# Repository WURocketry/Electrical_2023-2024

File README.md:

# Electrical
Electrical / Software Development

* Circuit CAD
* Software

### Subteam Folders
Subteams are free to modify their own folder as they like - keep all your subteam related files/articles/figures within that folder.

### Subteam Branches
The "main" Electrical repository is organized into 2 subteam development branches:

* "dev/avionics"
* "dev/payload"
* "dev/airbrakes"

Subteam changes should be pushed and pull requests made only to the respective development subteam branch!

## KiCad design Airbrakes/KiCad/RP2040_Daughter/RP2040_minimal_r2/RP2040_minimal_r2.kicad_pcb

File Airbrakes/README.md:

# Airbrakes Electrical

Folder for development of airbrake electrical mechanisms including:
> * Trajectory simulator
> * VLT
> * Actuation control algorithms
> * Eagle CADs

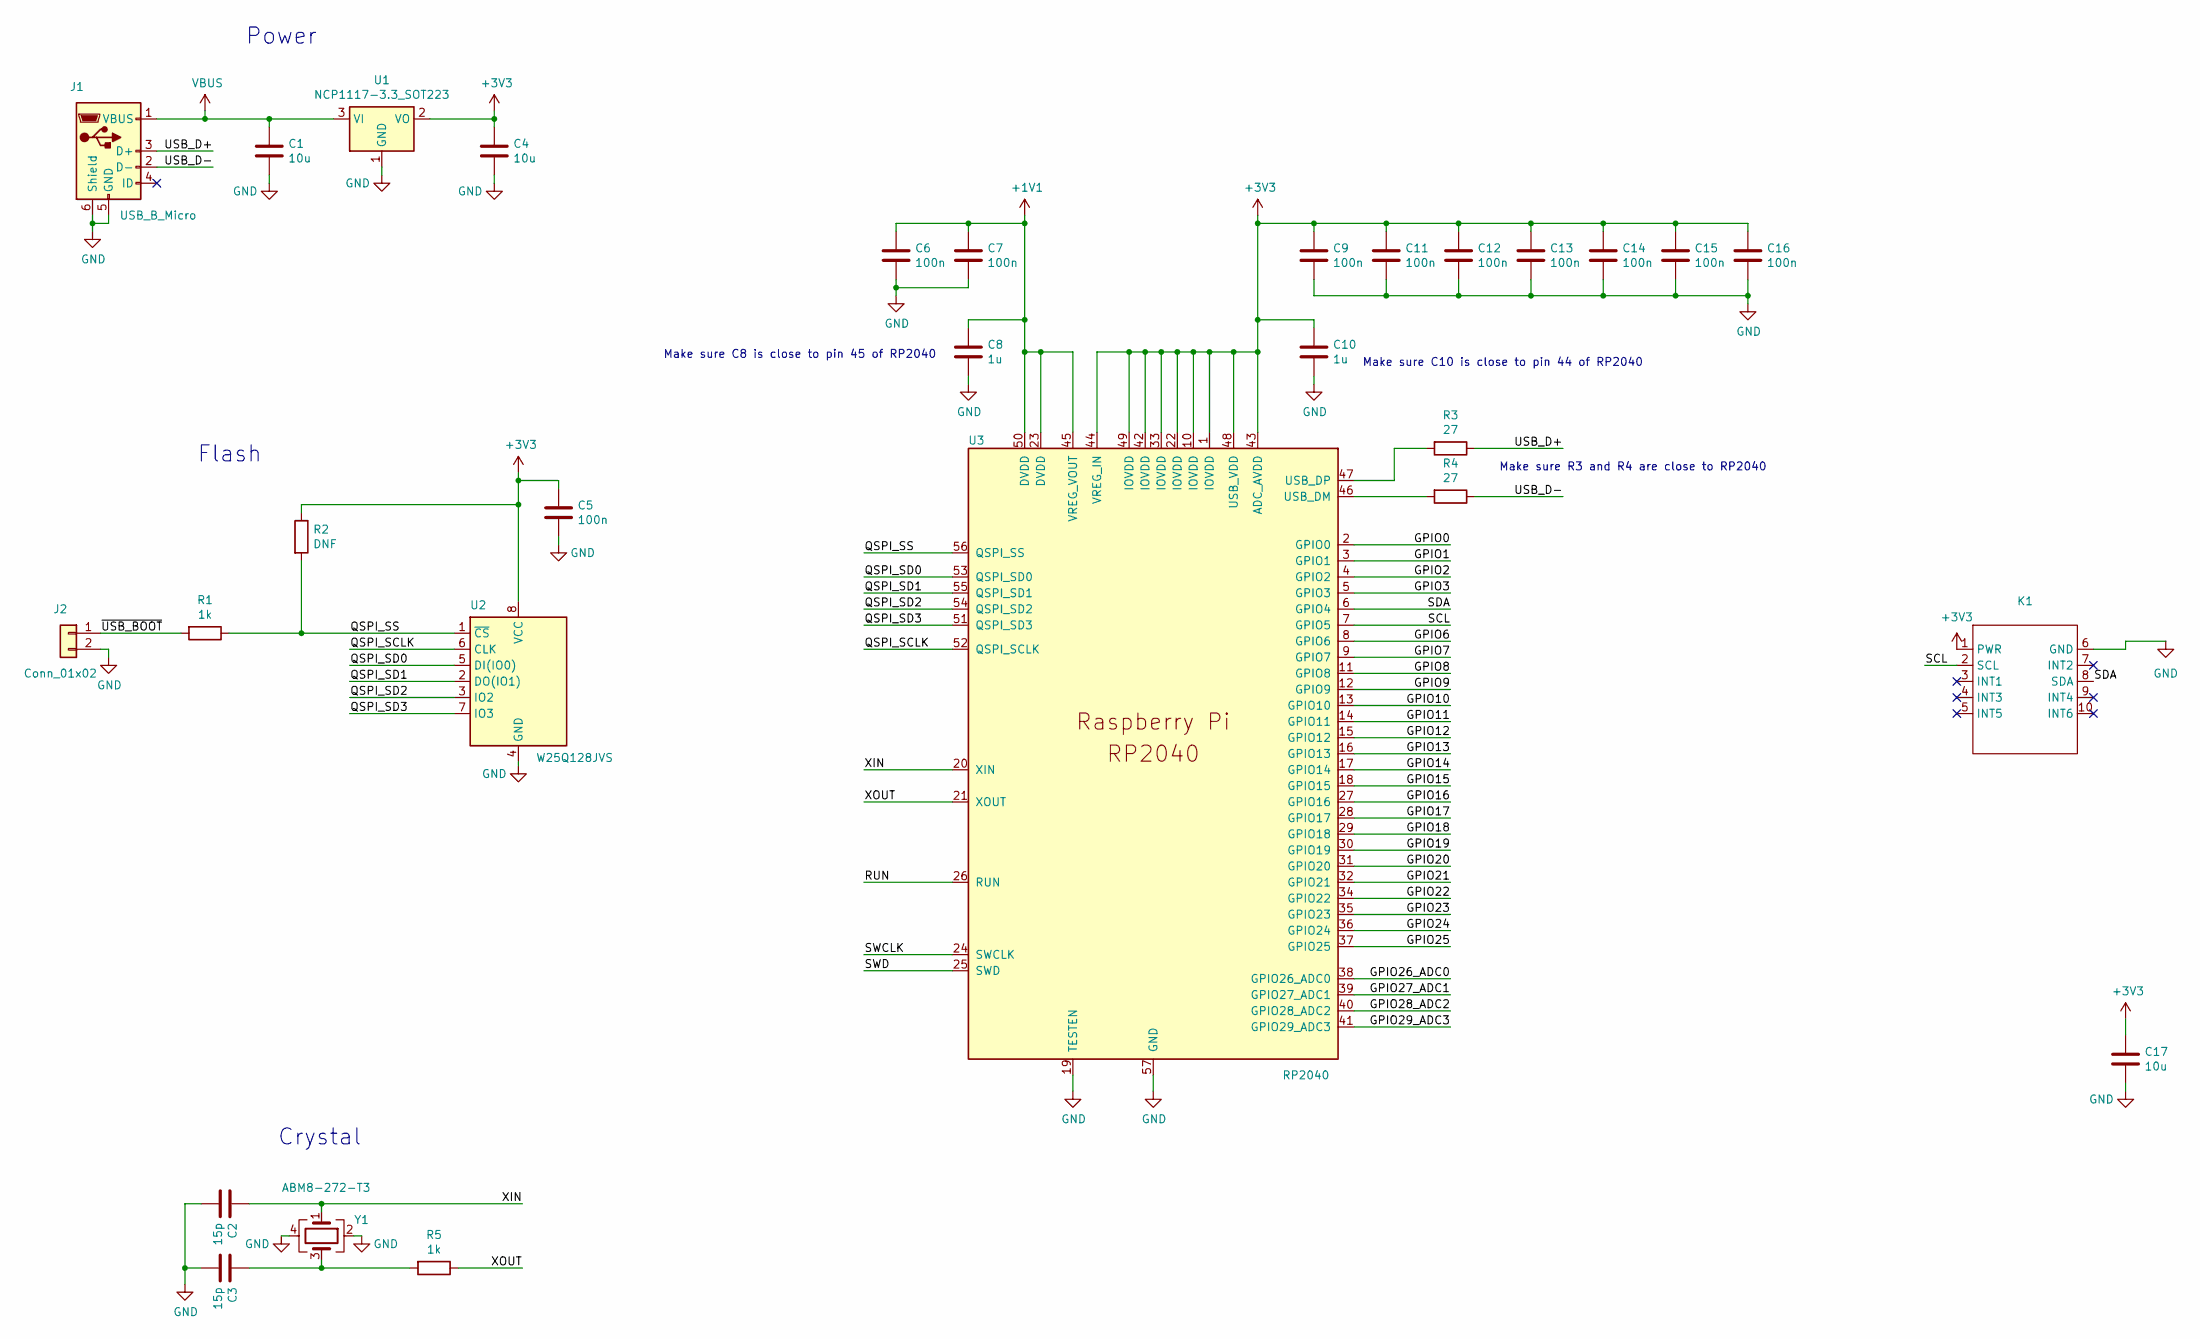
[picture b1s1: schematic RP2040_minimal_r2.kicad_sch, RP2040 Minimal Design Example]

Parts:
C1, C4, C17: 10u; C_0805_2012Metric
C2, C3: 15p; C_0402_1005Metric
C5, C6, C7, C9, C11, C12, C13, C14, C15, C16: 100n; C_0402_1005Metric
C8, C10: 1u; C_0402_1005Metric
J1: USB_B_Micro; USB_Micro-B_Amphenol_10103594-0001LF_Horizontal_modified
J2: Conn_01x02; PinHeader_1x02_P2.54mm_Vertical
K1: 12_Pin_Edge_Connector
R1, R5: 1k; R_0402_1005Metric
R2: DNF; R_0402_1005Metric
R3, R4: 27; R_0402_1005Metric
U1: NCP1117-3.3_SOT223; SOT-223-3_TabPin2
U2: W25Q128JVS; SOIC-8_5.23x5.23mm_P1.27mm
U3: RP2040; RP2040-QFN-56
Y1: ABM8-272-T3; Crystal_SMD_3225-4Pin_3.2x2.5mm

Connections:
+1V1: C6.1, C7.1, C8.1, U3.23 (DVDD), U3.45 (VREG_VOUT), U3.50 (DVDD)
+3V3: C4.1, C5.1, C9.1, C10.1, C11.1, C12.1, C13.1, C14.1, C15.1, C16.1, C17.1, K1.1 (PWR), R2.1, U1.2 (VO), U2.8 (VCC), U3.1 (IOVDD), U3.10 (IOVDD), U3.22 (IOVDD), U3.33 (IOVDD), U3.42 (IOVDD), U3.43 (ADC_AVDD), U3.44 (VREG_IN), U3.48 (USB_VDD), U3.49 (IOVDD)
/GPIO0: U3.2 (GPIO0)
/GPIO1: U3.3 (GPIO1)
/GPIO2: U3.4 (GPIO2)
/GPIO3: U3.5 (GPIO3)
/GPIO6: U3.8 (GPIO6)
/GPIO7: U3.9 (GPIO7)
/GPIO8: U3.11 (GPIO8)
/GPIO9: U3.12 (GPIO9)
/GPIO10: U3.13 (GPIO10)
/GPIO11: U3.14 (GPIO11)
/GPIO12: U3.15 (GPIO12)
/GPIO13: U3.16 (GPIO13)
/GPIO14: U3.17 (GPIO14)
/GPIO15: U3.18 (GPIO15)
/GPIO16: U3.27 (GPIO16)
/GPIO17: U3.28 (GPIO17)
/GPIO18: U3.29 (GPIO18)
/GPIO19: U3.30 (GPIO19)
/GPIO20: U3.31 (GPIO20)
/GPIO21: U3.32 (GPIO21)
/GPIO22: U3.34 (GPIO22)
/GPIO23: U3.35 (GPIO23)
/GPIO24: U3.36 (GPIO24)
/GPIO25: U3.37 (GPIO25)
/GPIO26_ADC0: U3.38 (GPIO26_ADC0)
/GPIO27_ADC1: U3.39 (GPIO27_ADC1)
/GPIO28_ADC2: U3.40 (GPIO28_ADC2)
/GPIO29_ADC3: U3.41 (GPIO29_ADC3)
/QSPI_SCLK: U2.6 (CLK), U3.52 (QSPI_SCLK)
/QSPI_SD0: U2.5 (DI(IO0)), U3.53 (QSPI_SD0)
/QSPI_SD1: U2.2 (DO(IO1)), U3.55 (QSPI_SD1)
/QSPI_SD2: U2.3 (IO2), U3.54 (QSPI_SD2)
/QSPI_SD3: U2.7 (IO3), U3.51 (QSPI_SD3)
/QSPI_SS: R1.1, R2.2, U2.1 (~CS), U3.56 (QSPI_SS)
/RUN: U3.26 (RUN)
/SCL: K1.2 (SCL), U3.7 (GPIO5)
/SDA: K1.8 (SDA), U3.6 (GPIO4)
/SWCLK: U3.24 (SWCLK)
/SWD: U3.25 (SWD)
/USB_D+: J1.3 (D+), R3.1
/USB_D-: J1.2 (D-), R4.1
/XIN: C2.1, U3.20 (XIN), Y1.1
/XOUT: R5.1, U3.21 (XOUT)
/~USB_BOOT: J2.1, R1.2
GND: C1.2, C2.2, C3.2, C4.2, C5.2, C6.2, C7.2, C8.2, C9.2, C10.2, C11.2, C12.2, C13.2, C14.2, C15.2, C16.2, C17.2, J1.5 (GND), J1.6 (Shield), J2.2, K1.6 (GND), U1.1 (GND), U2.4 (GND), U3.19 (TESTEN), U3.57 (GND), Y1.2, Y1.4
unnamed: C3.1, R5.2, Y1.3
unnamed: R4.2, U3.46 (USB_DM)
unnamed: R3.2, U3.47 (USB_DP)
VBUS: C1.1, J1.1 (VBUS), U1.3 (VI)

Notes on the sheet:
Power
Crystal
Make sure C8 is close to pin 45 of RP2040
Make sure C10 is close to pin 44 of RP2040
Make sure R3 and R4 are close to RP2040
Flash

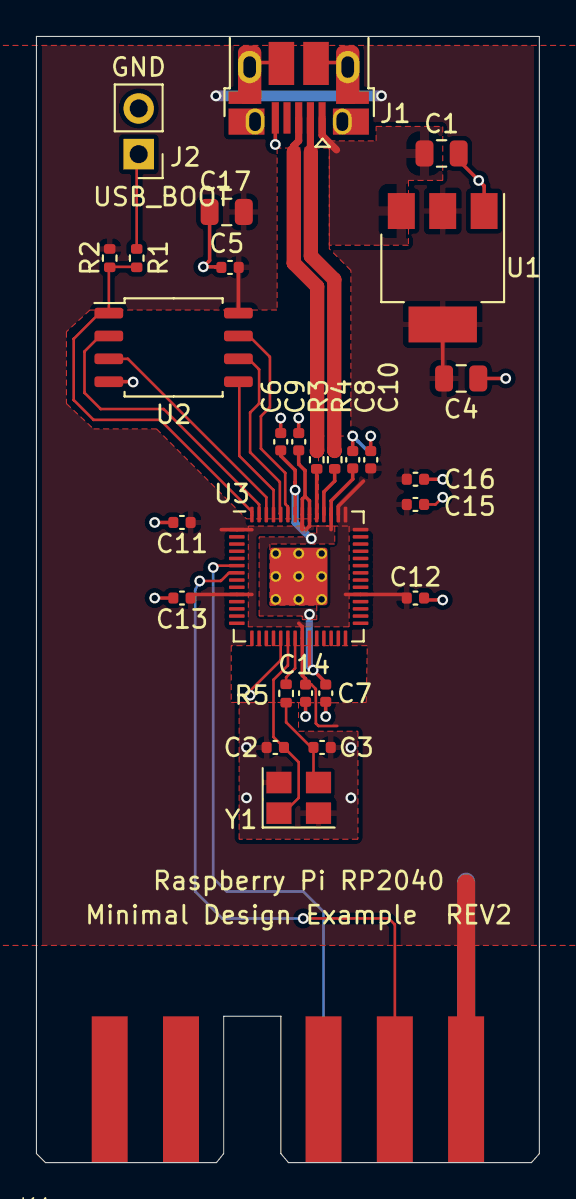
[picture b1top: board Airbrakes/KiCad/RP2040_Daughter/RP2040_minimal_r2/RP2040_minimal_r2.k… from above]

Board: 2 copper layers, 27.9 x 62.6 mm, 29 parts (0 on the bottom side), 20 nets.

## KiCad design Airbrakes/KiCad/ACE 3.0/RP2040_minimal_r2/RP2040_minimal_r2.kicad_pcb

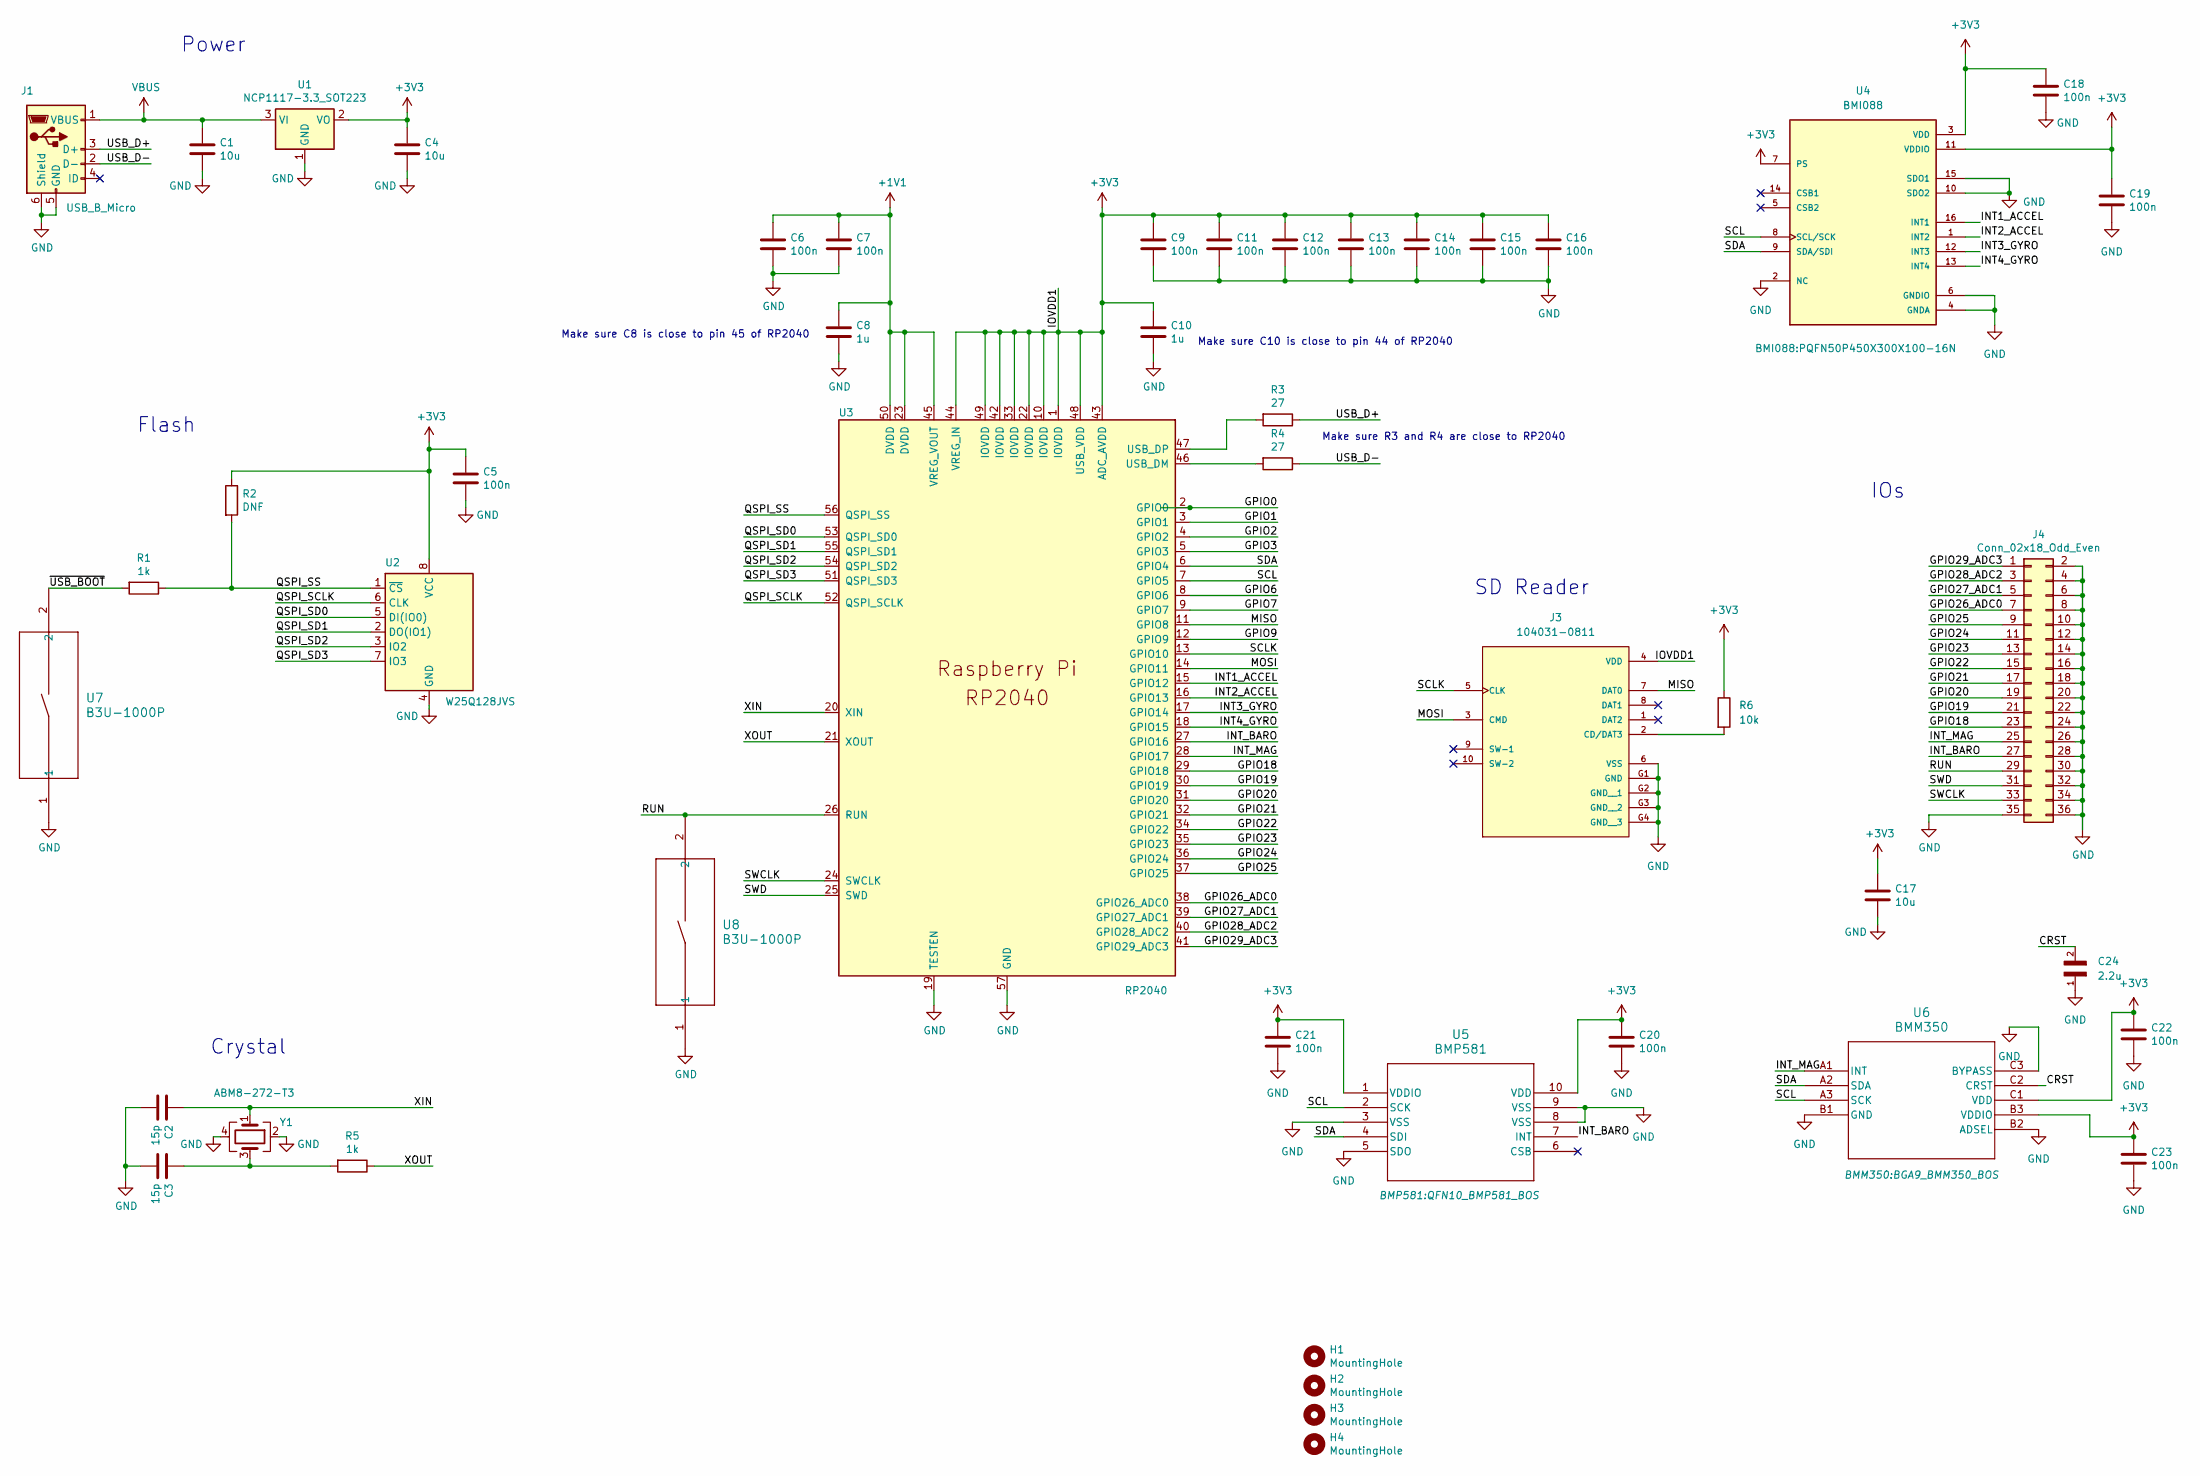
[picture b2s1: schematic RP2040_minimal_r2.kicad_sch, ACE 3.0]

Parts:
C1, C4, C17: 10u; C_0805_2012Metric
C2, C3: 15p; C_0402_1005Metric
C5, C6, C7, C9, C11, C12, C13, C14, C15, C16, C18, C19, C20, C21, C22, C23: 100n; C_0402_1005Metric
C8, C10: 1u; C_0402_1005Metric
C24: 2.2u; CAPC2012X55N
H1, H2, H3, H4: MountingHole; MountingHole_2.7mm_M2.5
J1: USB_B_Micro; USB_Micro-B_Amphenol_10103594-0001LF_Horizontal_modified
J3: 104031-0811; MOLEX_104031-0811; PARTREV B2
J4: Conn_02x18_Odd_Even; PinHeader_2x18_P2.54mm_Vertical
R1, R5: 1k; R_0402_1005Metric
R2: DNF; R_0402_1005Metric
R3, R4: 27; R_0402_1005Metric
R6: 10k; R_0402_1005Metric
U1: NCP1117-3.3_SOT223; SOT-223-3_TabPin2
U2: W25Q128JVS; SOIC-8_5.23x5.23mm_P1.27mm
U3: RP2040; RP2040-QFN-56
U4: BMI088; PQFN50P450X300X100-16N
U5: BMP581; QFN10_BMP581_BOS
U6: BMM350; BGA9_BMM350_BOS
U7, U8: B3U-1000P; SW_SPST_B3U-1000P
Y1: ABM8-272-T3; Crystal_SMD_3225-4Pin_3.2x2.5mm

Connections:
+1V1: C6.1, C7.1, C8.1, U3.23 (DVDD), U3.45 (VREG_VOUT), U3.50 (DVDD)
+3V3: C4.1, C5.1, C9.1, C10.1, C11.1, C12.1, C13.1, C14.1, C15.1, C16.1, C17.1, C18.1, C19.1, C20.1, C21.1, C22.1, C23.1, J3.4 (VDD), R2.1, R6.1, U1.2 (VO), U2.8 (VCC), U3.1 (IOVDD), U3.10 (IOVDD), U3.22 (IOVDD), U3.33 (IOVDD), U3.42 (IOVDD), U3.43 (ADC_AVDD), U3.44 (VREG_IN), U3.48 (USB_VDD), U3.49 (IOVDD), U4.3 (VDD), U4.7 (PS), U4.11 (VDDIO), U5.1 (VDDIO), U5.10 (VDD), U6.B3 (VDDIO), U6.C1 (VDD)
/CRST: C24.2, U6.C2 (CRST)
/GPIO0: U3.2 (GPIO0)
/GPIO1: U3.3 (GPIO1)
/GPIO2: U3.4 (GPIO2)
/GPIO3: U3.5 (GPIO3)
/GPIO6: U3.8 (GPIO6)
/GPIO7: U3.9 (GPIO7)
/GPIO9: U3.12 (GPIO9)
/GPIO18: J4.23, U3.29 (GPIO18)
/GPIO19: J4.21, U3.30 (GPIO19)
/GPIO20: J4.19, U3.31 (GPIO20)
/GPIO21: J4.17, U3.32 (GPIO21)
/GPIO22: J4.15, U3.34 (GPIO22)
/GPIO23: J4.13, U3.35 (GPIO23)
/GPIO24: J4.11, U3.36 (GPIO24)
/GPIO25: J4.9, U3.37 (GPIO25)
/GPIO26_ADC0: J4.7, U3.38 (GPIO26_ADC0)
/GPIO27_ADC1: J4.5, U3.39 (GPIO27_ADC1)
/GPIO28_ADC2: J4.3, U3.40 (GPIO28_ADC2)
/GPIO29_ADC3: J4.1, U3.41 (GPIO29_ADC3)
/INT1_ACCEL: U3.15 (GPIO12), U4.16 (INT1)
/INT2_ACCEL: U3.16 (GPIO13), U4.1 (INT2)
/INT3_GYRO: U3.17 (GPIO14), U4.12 (INT3)
/INT4_GYRO: U3.18 (GPIO15), U4.13 (INT4)
/INT_BARO: J4.27, U3.27 (GPIO16), U5.7 (INT)
/INT_MAG: J4.25, U3.28 (GPIO17), U6.A1 (INT)
/MISO: J3.7 (DAT0), U3.11 (GPIO8)
/MOSI: J3.3 (CMD), U3.14 (GPIO11)
/QSPI_SCLK: U2.6 (CLK), U3.52 (QSPI_SCLK)
/QSPI_SD0: U2.5 (DI(IO0)), U3.53 (QSPI_SD0)
/QSPI_SD1: U2.2 (DO(IO1)), U3.55 (QSPI_SD1)
/QSPI_SD2: U2.3 (IO2), U3.54 (QSPI_SD2)
/QSPI_SD3: U2.7 (IO3), U3.51 (QSPI_SD3)
/QSPI_SS: R1.1, R2.2, U2.1 (~CS), U3.56 (QSPI_SS)
/RUN: J4.29, U3.26 (RUN), U8.2
/SCL: U3.7 (GPIO5), U4.8 (SCL/SCK), U5.2 (SCK), U6.A3 (SCK)
/SCLK: J3.5 (CLK), U3.13 (GPIO10)
/SDA: U3.6 (GPIO4), U4.9 (SDA/SDI), U5.4 (SDI), U6.A2 (SDA)
/SWCLK: J4.33, U3.24 (SWCLK)
/SWD: J4.31, U3.25 (SWD)
/USB_D+: J1.3 (D+), R3.1
/USB_D-: J1.2 (D-), R4.1
/XIN: C2.1, U3.20 (XIN), Y1.1
/XOUT: R5.1, U3.21 (XOUT)
/~USB_BOOT: R1.2, U7.2
GND: C1.2, C2.2, C3.2, C4.2, C5.2, C6.2, C7.2, C8.2, C9.2, C10.2, C11.2, C12.2, C13.2, C14.2, C15.2, C16.2, C17.2, C18.2, C19.2, C20.2, C21.2, C22.2, C23.2, C24.1, J1.5 (GND), J1.6 (Shield), J3.6 (VSS), J3.G1 (GND), J3.G2 (GND__1), J3.G3 (GND__2), J3.G4 (GND__3), J4.2, J4.4, J4.6, J4.8, J4.10, J4.12, J4.14, J4.16, J4.18, J4.20, J4.22, J4.24, J4.26, J4.28, J4.30, J4.32, J4.34, J4.35, J4.36, U1.1 (GND), U2.4 (GND), U3.19 (TESTEN), U3.57 (GND), U4.2 (NC), U4.4 (GNDA), U4.6 (GNDIO), U4.10 (SDO2), U4.15 (SDO1), U5.3 (VSS), U5.5 (SDO), U5.8 (VSS), U5.9 (VSS), U6.B1 (GND), U6.B2 (ADSEL), U6.C3 (BYPASS), U7.1, U8.1, Y1.2, Y1.4
unnamed: C3.1, R5.2, Y1.3
unnamed: J3.2 (CD/DAT3), R6.2
unnamed: R4.2, U3.46 (USB_DM)
unnamed: R3.2, U3.47 (USB_DP)
VBUS: C1.1, J1.1 (VBUS), U1.3 (VI)

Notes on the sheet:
IOs
Power
Crystal
Make sure C8 is close to pin 45 of RP2040
SD Reader
Make sure C10 is close to pin 44 of RP2040
Make sure R3 and R4 are close to RP2040
Flash

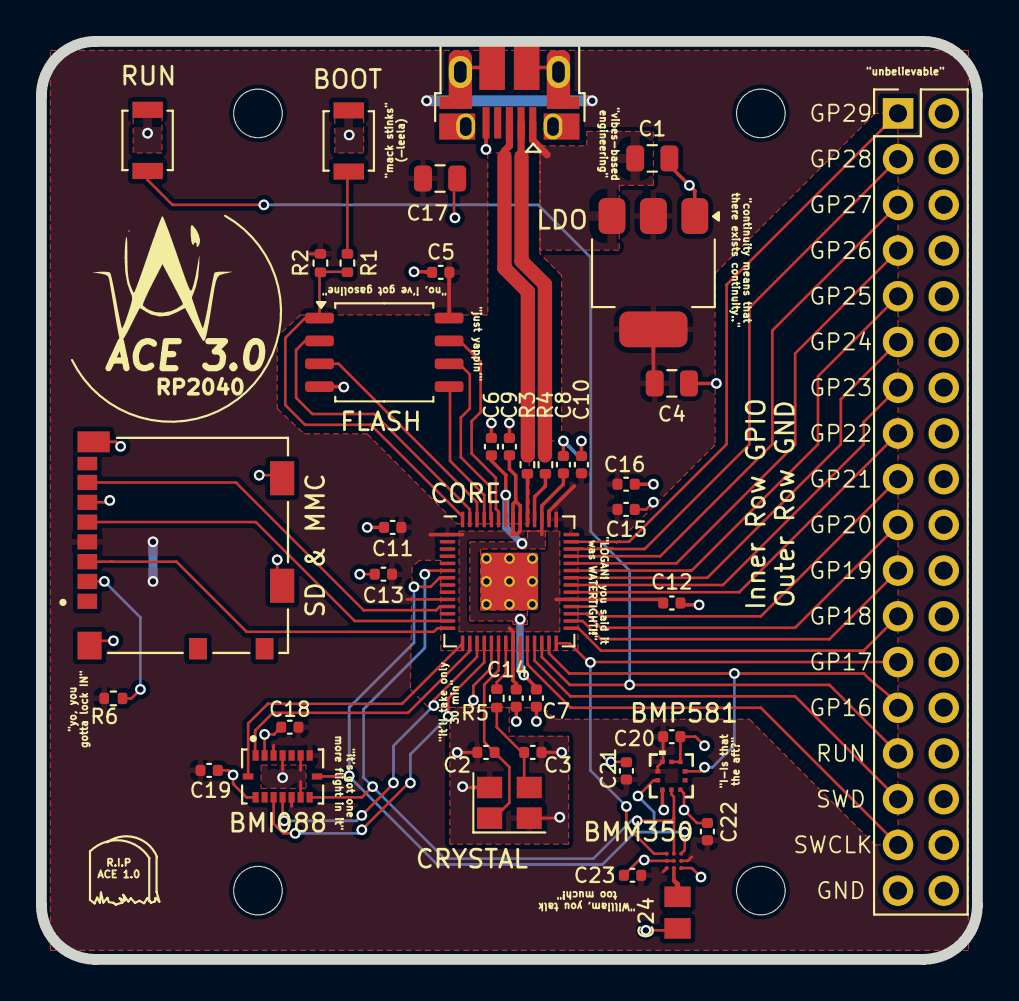
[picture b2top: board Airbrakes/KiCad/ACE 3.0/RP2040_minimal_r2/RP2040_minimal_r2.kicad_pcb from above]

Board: 2 copper layers, 52.0 x 51.0 mm, 46 parts (0 on the bottom side), 46 nets.

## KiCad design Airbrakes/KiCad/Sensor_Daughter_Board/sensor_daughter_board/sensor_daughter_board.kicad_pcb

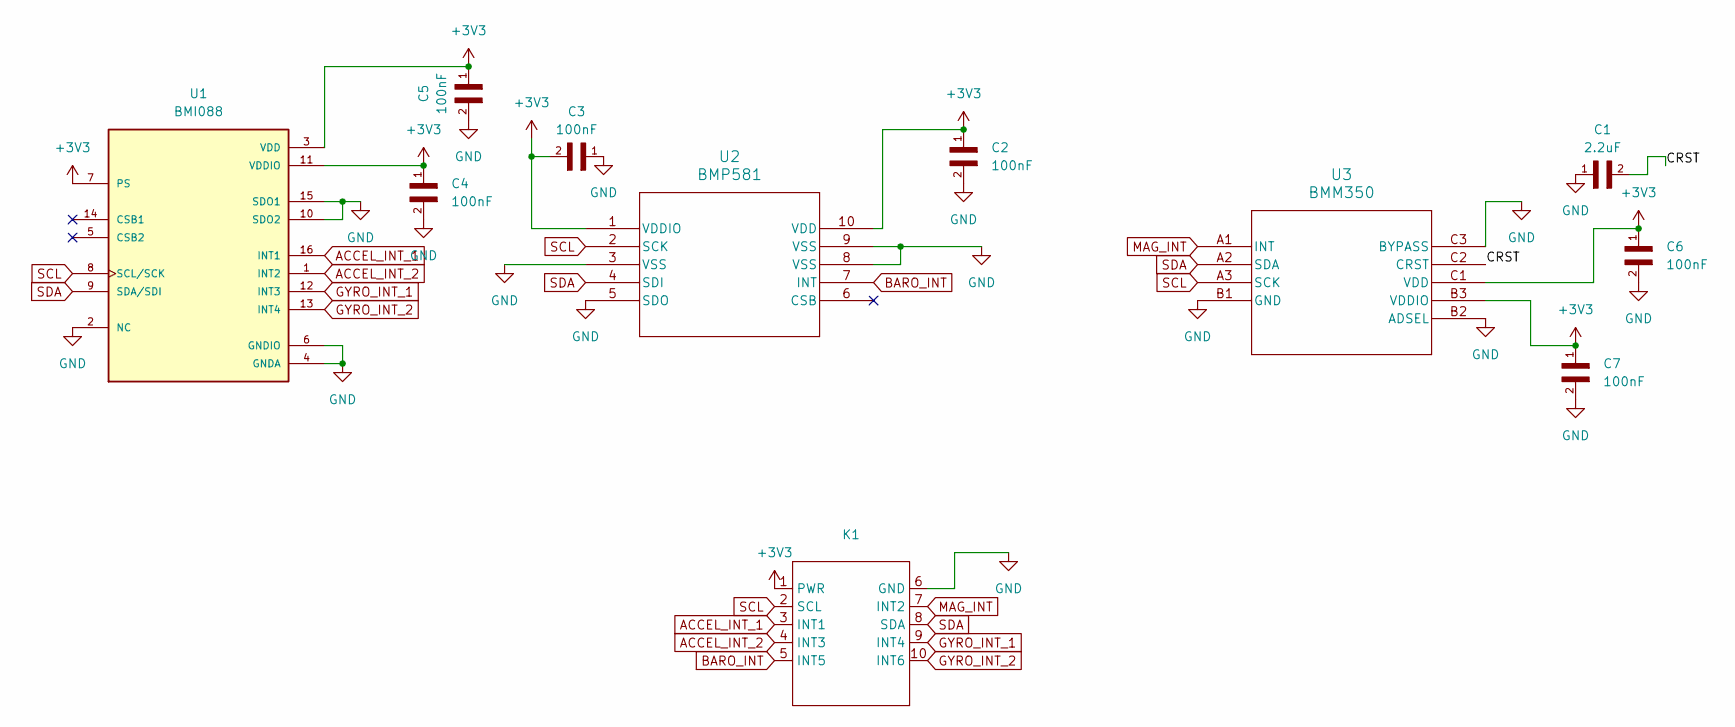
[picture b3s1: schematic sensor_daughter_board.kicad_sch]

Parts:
C1: 2.2uF; CAPC2012X55N
C2, C3, C4, C5, C6, C7: 100nF; CAPC1005X55N
K1: 12_Pin_Edge_Connector
U1: BMI088; PQFN50P450X300X100-16N
U2: BMP581; QFN10_BMP581_BOS
U3: BMM350; BGA9_BMM350_BOS

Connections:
+3V3: C2.1, C3.2, C4.1, C5.1, C6.1, C7.1, K1.1 (PWR), U1.3 (VDD), U1.7 (PS), U1.11 (VDDIO), U2.1 (VDDIO), U2.10 (VDD), U3.B3 (VDDIO), U3.C1 (VDD)
/CRST: C1.2, U3.C2 (CRST)
ACCEL_INT_1: K1.3 (INT1), U1.16 (INT1)
ACCEL_INT_2: K1.4 (INT3), U1.1 (INT2)
BARO_INT: K1.5 (INT5), U2.7 (INT)
GND: C1.1, C2.2, C3.1, C4.2, C5.2, C6.2, C7.2, K1.6 (GND), U1.2 (NC), U1.4 (GNDA), U1.6 (GNDIO), U1.10 (SDO2), U1.15 (SDO1), U2.3 (VSS), U2.5 (SDO), U2.8 (VSS), U2.9 (VSS), U3.B1 (GND), U3.B2 (ADSEL), U3.C3 (BYPASS)
GYRO_INT_1: K1.9 (INT4), U1.12 (INT3)
GYRO_INT_2: K1.10 (INT6), U1.13 (INT4)
MAG_INT: K1.7 (INT2), U3.A1 (INT)
SCL: K1.2 (SCL), U1.8 (SCL/SCK), U2.2 (SCK), U3.A3 (SCK)
SDA: K1.8 (SDA), U1.9 (SDA/SDI), U2.4 (SDI), U3.A2 (SDA)

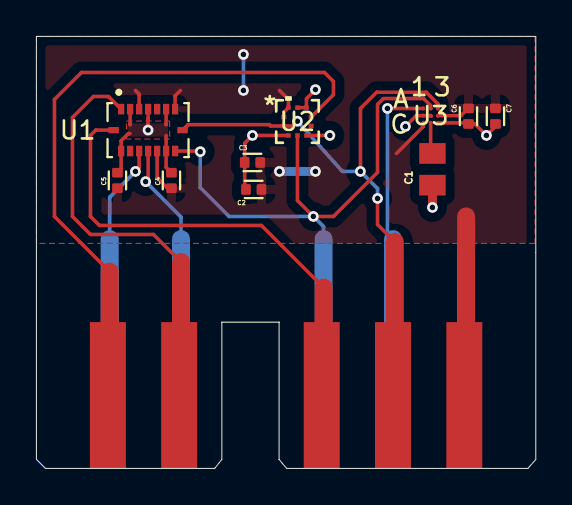
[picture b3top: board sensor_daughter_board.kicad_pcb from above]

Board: 2 copper layers, 27.7 x 24.0 mm, 11 parts (0 on the bottom side), 11 nets.

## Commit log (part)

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2023-10-22 Fixed delta timing from comments
2023-10-22 base station script
2023-10-22 Update main.cpp
    Updated standby state
2023-10-22 Initial FSM integration for ACE (#47)
    * Update main.cpp
    Implemented FSM transitions
    * Update main.cpp
    Updated standby state
    ---------
2023-10-23 Create vlt.h
    Creates velocity look-up table for Full Scale as header file
2023-10-24 move vlt table
2023-10-24 fixing merge conflicts
2023-10-25 Modified delta timing and changed time status to unsigned long
2023-10-25 Add BAD approximations for mass change over time and drag dependence on Vel
2023-10-25 Make delta timing discrete and replace COMPUTE poll condition
    * Last time variables are incremented by respective delta times
    * COMPUTE runs at multiples of 4 SAMPLE polls
2023-10-25 Delta timing for components (#46)
    * Fixed delta timing from comments
    * Fixed delta timing, no compiler errors
    * Modified delta timing and changed time status to unsigned long
    ---------
2023-10-29 adding neopixel stuff, compiles
2023-10-29 Revert "Payload/small csv"
2023-11-01 FlightMonitor header file
2023-11-01 LinearInterp attempt
2023-11-01 PID Control/Servo Test Control File
2023-11-01 Update main.ino (#54)
    * Update main.ino
    * Update main.ino
2023-11-02 Add simulation OR data sample
2023-11-02 Add necessary files and definitions
2023-11-03 Add necessary files and definitions (#57)
2023-11-03 Add simulation OR data sample (#56)
    * Add simulation OR data sample
    * Handle negative simulation time exception case
    ---------
2023-11-03 Implement all state transtions
2023-11-03 Create Persistences
    landing transition does not behave as expected.
2023-11-04 Fix Bounds
2023-11-04 hello world on receiving end and server end both work
2023-11-04 Change persistence and remove include
2023-11-04 Added not about removing wait for serial connection for flight
2023-11-04 Attempt at preprocessor stuff
    Also added something to .ini to make the sdram.h work... it did not
2023-11-05 Implement all state transitions (#58)
    * Implement all state transtions
    * Create Persistences
    landing transition does not behave as expected.
    * Move Evaluation of Flight Monitor
    * Fix Bounds
    * create ringBuffer for data storage
2023-11-05 bme680 delta timing test
2023-11-05 Draft PID header file
2023-11-06 Added linear interp
2023-11-08 Update PID header file
2023-11-08 state vector API work
2023-11-08 new radio integration
2023-11-09 add IMU platformIO port
2023-11-09 Fix SDRAM init and test successful physical build
2023-11-09 Added servo library
2023-11-10 Review PID controller
2023-11-10 Implement PID controller into ACE
2023-11-10 Draft PID header file (#61)
    * Draft PID header file
    * Update PID header file
    * Prototype of PID_controller class
    * changed error
    * Added servo library
    * Review PID controller
2023-11-10 allow code to work on RP2040
2023-11-10 encapsulate kalman stuff into header file
    I re-activated the simulation BTW
2023-11-10 small fixes
2023-11-10 Integrated BNO085
2023-11-11 update VLT
2023-11-11 update Simulation
2023-11-11 add quaternions
2023-11-11 ALtitude readings
2023-11-11 Collect sensor data
2023-11-11 sync analysis files
2023-11-11 Implement measurement structs
2023-11-11 Update sample (IMU/Alt) frequency (100Hz) and compute frequency (100Hz)
2023-11-11 Create accel Replace
2023-11-11 add acceleration Replacement
2023-11-11 Change SDRAM size to record 5 minutes of flight
2023-11-11 Remove additional variables (for now)
2023-11-11 PID fix investigation
2023-11-12 Clean up FlightMon and kalman defines
2023-11-12 Fix flight monitor init
2023-11-12 PID fixes
2023-11-12 Servo control only in control phase
2023-11-12 First flight-ready prototype build
2023-11-15 Added rp2040 support
2023-11-15 time testing
2023-11-15 Revert "added new array"
    This reverts commit a46a1262b01a06a3490d61831517f0d6ea0d2fea.
    dd
2023-11-15 Revert "Revert "added new array""
    This reverts commit e6800fba9e1aacb9877302714bf646f0352c25b9.
    dfdsf
2023-11-15 Fix rotation vector for inertial frame
2023-11-19 delta timing test
2023-11-19 test
2023-11-19 Autumn's Updates + Main Fixes
2023-11-19 stateVec api functions
2023-11-19 make i2c run faster
2023-11-29 Temp comment Wire crash fix
2023-12-08 added servo library import statement
2023-12-08 Hmm, maybe this servo stuff will work
2023-12-09 changed control line at end to use new servo step function instead of writing direct to servo
2023-12-09 Made most changes that Brendan requested.
2023-12-10 Finalize v0.2 ACE PCB
2023-12-14 Add CAM job for ACEv0.2
2023-12-14 Minor reformatting
2023-12-14 Payload/asynchronus bme (#68)
    * BME Asynchronus Reading
    * bme680 delta timing test
    * delta timing test
    * test
    ---------
2023-12-14 Add pre-flight configuration
2023-12-14 Reorganization for linkage order and static storage
2023-12-15 Restructure airbrakes code directories
2023-12-15 Refactor FSM definitions into namespace
2023-12-15 Refactor measurement code and simplify sensor sample includes
2023-12-15 initial investigation
2023-12-16 Add initialization checks
2023-12-16 Implement Adafruit ADXL345 sensor
2023-12-17 Fix BMP388 calibration didInit bug
2023-12-17 Modify sensor integration and support ADXL345 linear acceleration measurement
2023-12-17 Update OpenLogger class instance and fix init
2023-12-17 Move OpenLog into component class (#84)
    * Move openlog into component class
    * Add initialization checks
    * Update OpenLogger class instance and fix init
    ---------
2023-12-17 Fix FlightMonitor pass-by-value copy bug
2023-12-17 Airbrakes/investigate fm update (#85)
    * initial investigation
    * Fix FlightMonitor pass-by-value copy bug
2023-12-17 Add servo actuation init check
2023-12-17 Invert servo angle control and add development mode prints/sim
2023-12-17 Flight changes
2023-12-18 Subscale launch changes and servo range tweaks
2024-01-12 Create stale.yml test (#89)
    Testing gh actions
2024-01-12 Update pio-build-airbrakes.yml
    Point all run working directories to Pio root by default
2024-01-12 Merge test GH Actions (#91)
    * Create stale.yml test
    Testing gh actions
    * Create pio-build-airbrakes.yml
    PlatformIO build workflow for Airbrakes
    * Update pio-build-airbrakes.yml
    Point all run working directories to Pio root by default
2024-01-12 Move .github/workflows/pio-build-airbrakes.yml to dev/airbrakes
    Deleting file to move to correct workflow branch
2024-01-12 Add pio build workflow
2024-01-12 aaand move directory because I am blind
2024-01-14 Update pio-build.yml
    Modify for PR trigger
2024-01-14 Sync pio-build.yml
    From dev/airbrakes
2024-01-14 Sync auto-assign.yml
    from main
2024-01-14 Add mock file
2024-01-14 Mock updates with changes
2024-01-14 Sync pio-build.yml
    from main
2024-01-14 Update pio-build.yml
    Add gh_token for CLI access
2024-01-14 Update pio-build.yml
    Check relevant changes after github checkout
2024-01-14 Update pio-build.yml
    Fix gh token and git diff
2024-01-14 Yet another test of irrelevant change
2024-01-14 testing again, irrelevant change
2024-01-14 now, making a relevant change in the relevant directory...
2024-01-14 another relevant change
2024-01-14 Update pio-build.yml
    Fix dorny filter
2024-01-14 changed
2024-01-14 test push with faulty code
2024-01-19 Add Unified Sensor lib
2024-01-19 fixes
2024-01-19 updating platformio
2024-01-20 platformio bugfixing
2024-01-20 Fix EEPROM include and successful target compilation
2024-01-27 Added tilt detection
2024-01-28 Reorganize file structure
2024-01-30 Test payload
2024-01-30 update with change filter
2024-01-30 Test pio build in project
2024-01-30 removed file in test pio path
2024-01-30 Add gh action workflows
2024-02-04 servo class changes
2024-02-07 Added tilt fault protection and stow method
2024-02-08 Added standby transition to FSM
2024-02-09 trying to fix gps
2024-02-09 Add servo updates during controlStandby state
2024-02-10 Minor degree offset config for aft assembly
2024-02-10 FS VLT
2024-02-11 trim data that transmit live
2024-02-13 PACE Start
2024-02-13 New mavlink python script added
2024-02-14 First draft of PACE
2024-02-14 Add MPM3630 block
2024-02-14 Add 51 Ohm resistor part
2024-02-15 added base station code
2024-02-18 fixed bug
2024-02-19 Reorganize local EAGLE files
2024-02-19 Reorganize PACE to new project folder
2024-02-19 Move EAGLE into subteam independent folder
2024-02-19 Add PCE trace width test EAGLE
2024-02-25 Move ACE complete message into loop
2024-02-25 Add forced extension and status led options
2024-02-26 Fix dimensions
2024-02-27 Update USB-C with Molex mfg part
2024-03-08 fix_datalog
2024-03-09 attempt
2024-03-21 Create LOGGING_TEST.ino
    openlog test
2024-03-21 initial script update
2024-03-21 updated error handling
2024-03-22 abbys files
2024-03-22 control flow refining
2024-03-22 base station transmit from avionics/nasir
2024-03-22 change the reconnection sequence
2024-03-23 Update main.ino
    shifted .append() call in logData and removed .appen() call in setup
2024-03-23 changed port
2024-03-23 launch day telemetry
2024-03-24 LOGGING_TEST
    fixed logging test
2024-03-24 Cleaning the code
2024-03-25 Modifications from Sunday's test
2024-03-26 drone control modifications
2024-03-28 adding the new life metrics code
2024-03-28 added neoPixel code to life_metrics_reborn
2024-03-28 python script runs on boot and drone connection error handling works
2024-03-28 Add code to pull mosfet gates to low on startup
2024-03-28 to clean status log file
2024-03-29 miscellaneous during testing
2024-03-29 changing
2024-03-29 Rename rc.local to rc.local_code
2024-03-29 updated alaunch day receive
2024-03-31 deleted !serial line
2024-04-04 changes to init order
2024-04-04 updated packet status enum
2024-04-04 documentation
2024-04-04 copypasta from Adafruit ADXL345
2024-04-05 accelorometer work
2024-04-06 rewrote error led a bit
2024-04-07 Clarify error decay function
2024-04-10 nothing?
2024-04-13 updating baseline for spg
2024-04-13 Radio calculation
2024-04-21 VLT investigation
2024-04-21 Document Kalman.h
2024-04-21 Fix library dependencies
2024-04-21 ACE 3.0
2024-04-21 Velocity Look-up table work
2024-04-22 make slight changes to ACE 3.0
2024-04-23 fix some labelling on schematic for ACE 3.0
2024-04-24 Project documentation + READMEs
2024-04-24 Document EAGLE/
2024-05-03 Beginning refactor + add local libraries folder
2024-05-04 sd card interfacing
2024-05-04 Update traces
2024-05-05 Redraw left power plane
2024-05-05 Test pour again
2024-05-05 loose wire test
2024-05-05 changed cs_sd to pull-up and fixed csb
2024-05-05 refilled pcb
2024-05-05 WIP wiring + DRC checks
2024-05-05 Fix gnd connection
2024-05-06 New Sensor Board - No pringles
2024-05-06 Kicad prototype/sd card (#110)
    * sd card interfacing
    * updated traces
    * Update traces
    * Updated traces
    * Redraw left power plane
    * Update RP2040_minimal_r2.kicad_pcb
2024-05-06 deleted everything (aka moved files around)
2024-05-06 make traces larger for PWR and GND
2024-05-06 Fix DRC unconnections
2024-05-06 Update Symbol for edge connector
2024-05-06 RP2040 Daughter Board
2024-05-06 Update .gitignore + rm cache file
2024-05-06 Final routing draft + DRC fixes
2024-05-06 Silkscreen
2024-05-06 DRC warning fixes
2024-05-06 Update footprint refs
2024-05-07 Final review + DRC pass
2024-05-07 make edge connected .2 mm smaller
2024-05-07 silkscreens
2024-05-07 Finalize KiCad prototype of ACE 3.0 (#111)
    * Beginning refactor + add local libraries folder
    * Kicad prototype/sd card (#110)
    * sd card interfacing
    * updated traces
    * Update traces
    * Updated traces
2024-05-07 Merge dev/airbrakes to 2023-2024 Electrical (#106)
    * init Airbrakes folder
    * Added data and barebones simulation
    * Update README.md
    * LaunchAndControlSim
    * update controller with drag VLT and integral term
    * change errorDecay to be dependent on altitude
